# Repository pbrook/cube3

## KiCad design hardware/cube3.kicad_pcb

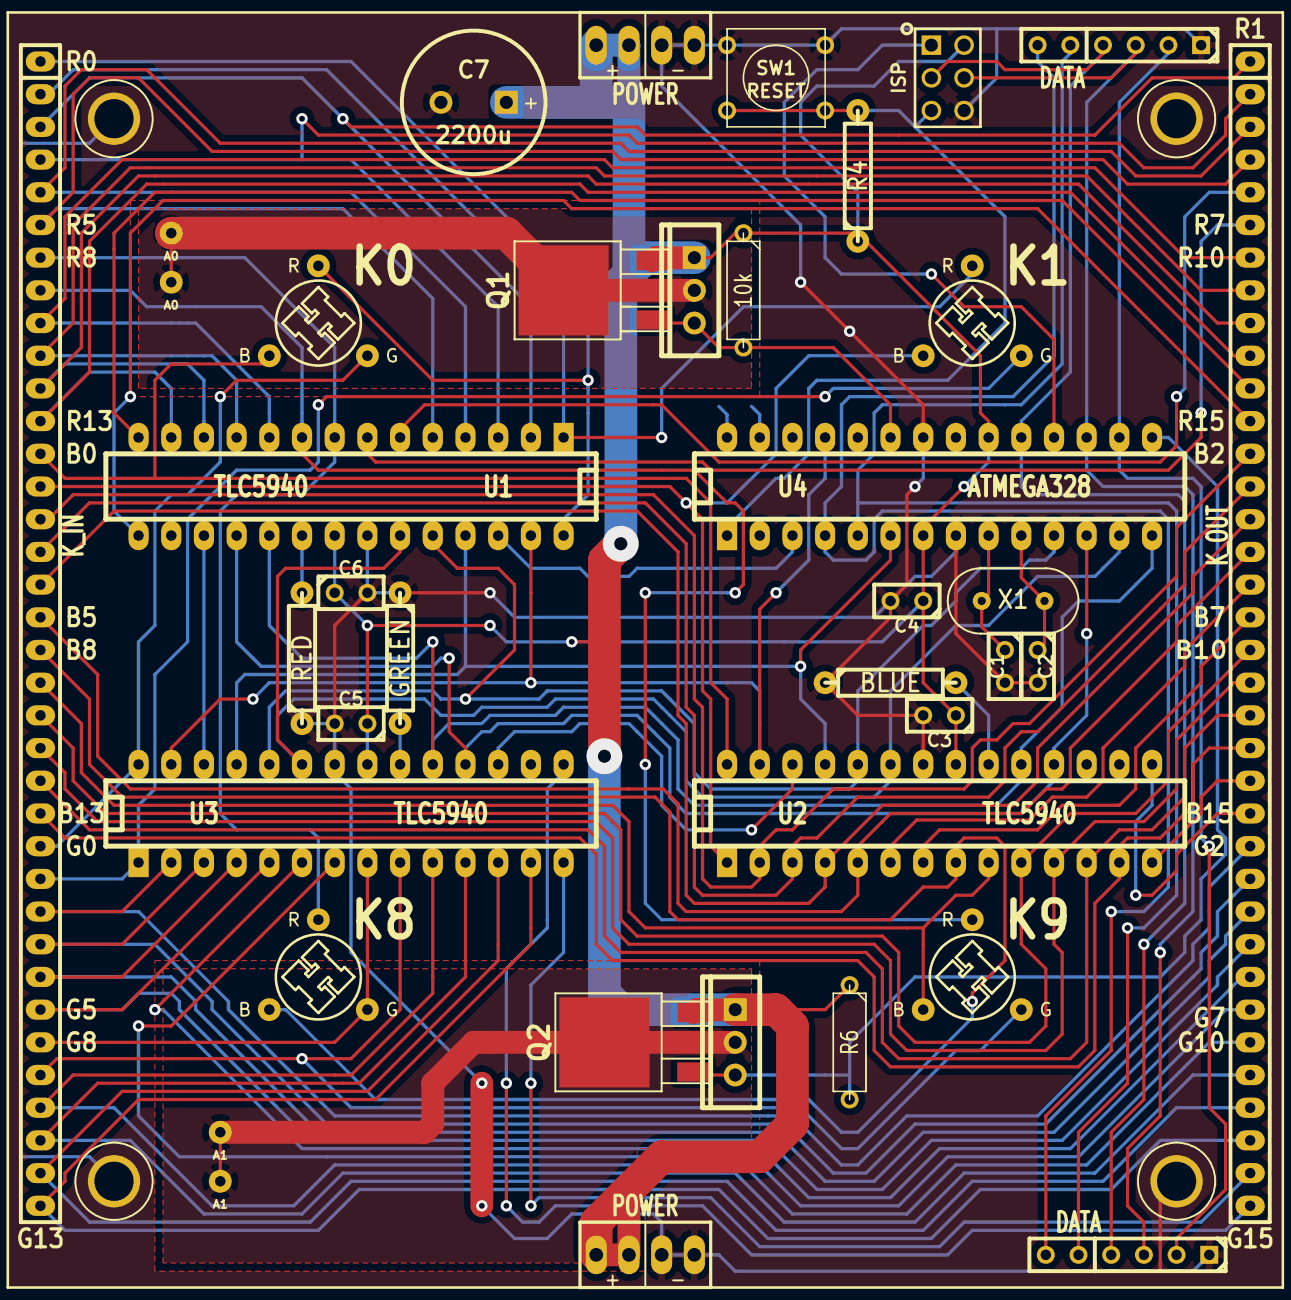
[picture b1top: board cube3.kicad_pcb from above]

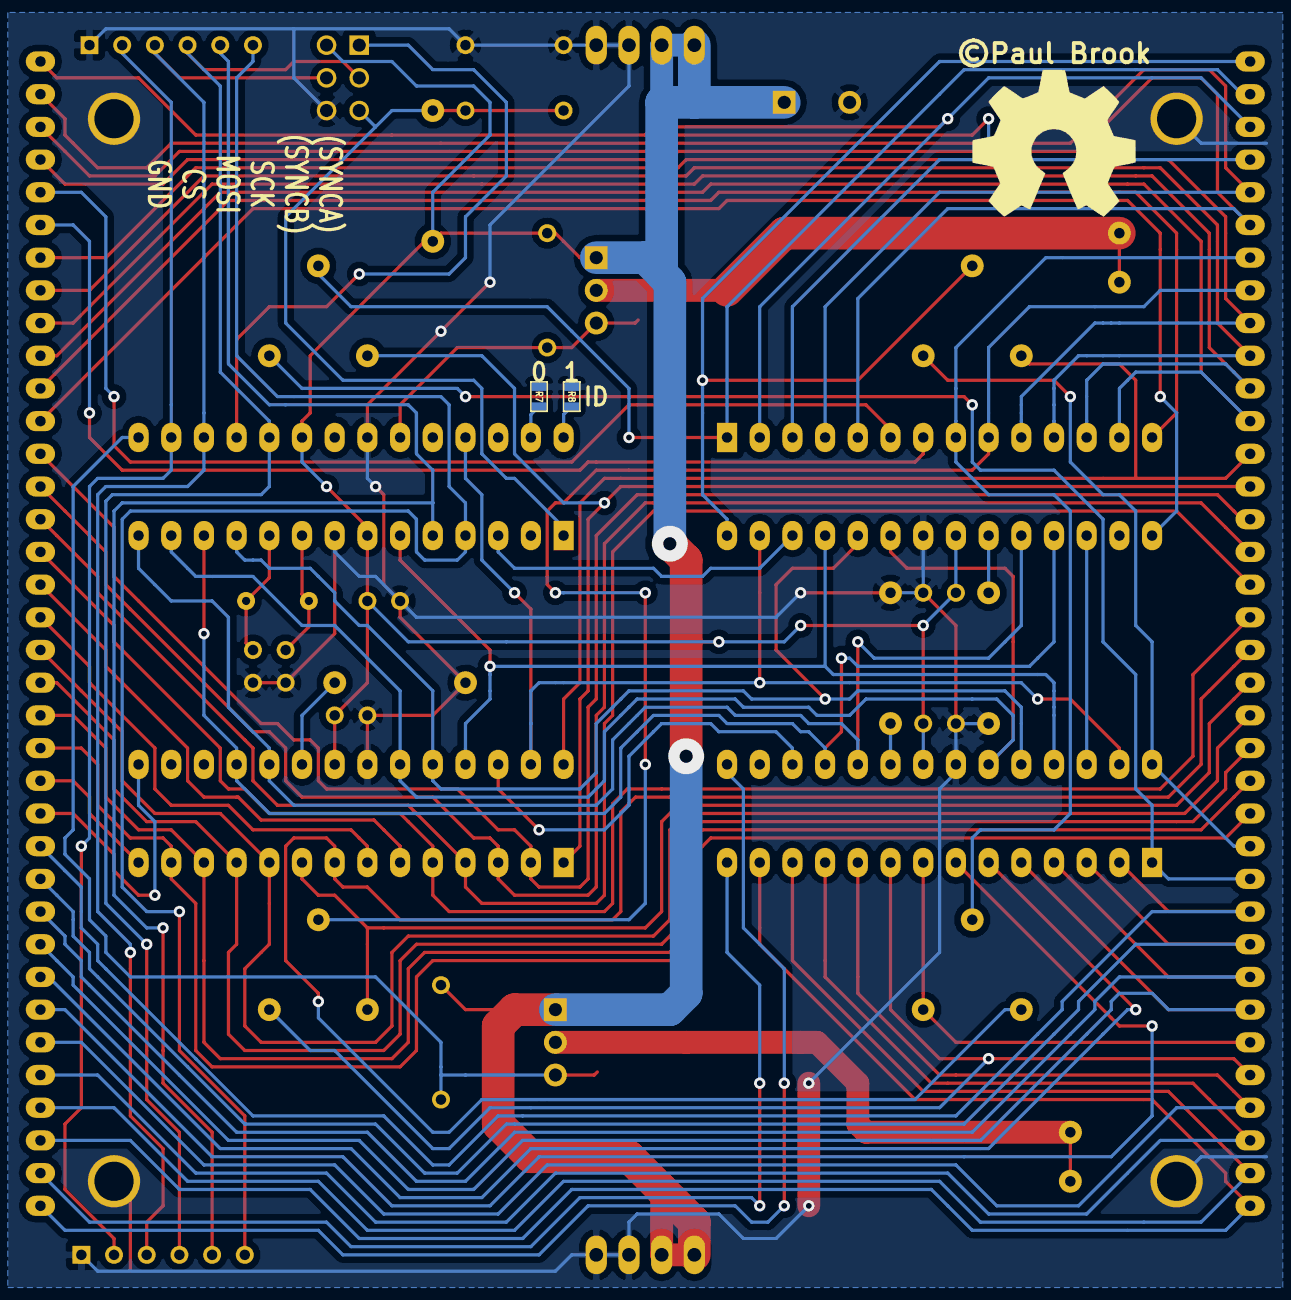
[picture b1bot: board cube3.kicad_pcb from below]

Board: 2 copper layers, 44 parts (2 on the bottom side), 77 nets.

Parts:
C1, C2: 22p; C1
C3, C4, C5, C6: 100n; C1
C7: 2200u; CP2V10
K0, K1, K8, K9: RGB_CATHODE; rgb_cathode
P1, P2: POWER; power2
P3, P4: DATA; SIL-6
P5: ISP; isp
P6, P7: A0; PIN1
P8, P15: A1; PIN1
P9: K_OUT; SIL-36
P10: K_IN; SIL-36
P11, P12, P13, P14: CONN_1; HOLE3
Q1, Q2: AP4435GH; to252
Q3, Q4: CONN_3; TO220_VERT
R1: RED; R4-LARGE_PADS
R2: BLUE; R4-LARGE_PADS
R3: GREEN; R4-LARGE_PADS
R4: 10k; R4-LARGE_PADS
R5, R6: 10k; R3-5
R7, R8: 0; SM0603
SW1: RESET; SW_PUSH_SMALL
U1, U2, U3: TLC5940; DIP-28__300_ELL
U4: ATMEGA328; DIP-28__300_ELL
X1: 16MHz; Crystal

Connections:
/5v: C3.1, C4.1, C5.1, C6.1, C7.1, P1.2, P2.2, P5.2, Q1.S, Q2.S, Q3.1, Q4.1, R4.1, R5.1, R6.1, U1.21, U2.21, U3.21, U4.7, U4.20
/A0: Q1.G, Q3.2, R5.2, U4.23
/A1: Q2.G, Q4.2, R6.2, U4.15
/BLANK: U1.23, U2.23, U3.23, U4.13
/BREF: R2.2, U2.20
/CS: P3.2, P4.2, U4.16
/DCPRG: U1.19, U2.19, U3.19, U4.14
/GND: C1.2, C2.2, C3.2, C4.2, C5.2, C6.2, C7.2, P1.1, P2.1, P3.1, P4.1, P5.6, P11.1, P12.1, P13.1, P14.1, R1.1, R2.1, R3.1, R7.1, R8.1, SW1.1, U1.22, U2.22, U3.22, U4.8, U4.22
/GREF: R3.2, U3.20
/GSCK: U1.18, U2.18, U3.18, U4.12
/H0: P6.1, P7.1, Q1.D, Q3.3
/H1: P8.1, P15.1, Q2.D, Q4.3
/ID0: R7.2, U4.27
/ID1: R8.2, U4.28
/MISO: P5.1, U4.18
/MOSI: P3.3, P4.3, P5.4, U4.17
/RESET: P5.5, R4.2, SW1.2, U4.1
/RREF: R1.2, U1.20
/SCK: P3.4, P4.4, P5.3, U4.19
/SCLK: U1.25, U2.25, U3.25, U4.6
/SIN: U1.26, U4.3
/SYNCA: P3.6, P4.6, U4.4
/SYNCB: P3.5, P4.5, U4.5
/VPRG: U1.27, U2.27, U3.27, U4.25
/XLAT: U1.24, U2.24, U3.24, U4.11
/b0: K0.B, P10.13, U2.28
/b1: K1.B, P10.14, U2.1
/b2: P9.13, P10.15, U2.2
/b3: P9.14, P10.16, U2.3
/b4: P9.15, P10.17, U2.4
/b5: P9.16, P10.18, U2.5
/b6: P9.17, U2.6
/b7: P9.18, U2.7
/b8: K8.B, P10.19, U2.8
/b9: K9.B, P10.20, U2.9
/b10: P9.19, P10.21, U2.10
/b11: P9.20, P10.22, U2.11
/b12: P9.21, P10.23, U2.12
/b13: P9.22, P10.24, U2.13
/b14: P9.23, U2.14
/b15: P9.24, U2.15
/g0: K0.G, P10.25, U3.28
/g1: K1.G, P10.26, U3.1
/g2: P9.25, P10.27, U3.2
/g3: P9.26, P10.28, U3.3
/g4: P9.27, P10.29, U3.4
/g5: P9.28, P10.30, U3.5
/g6: P9.29, U3.6
/g7: P9.30, U3.7
/g8: K8.G, P10.31, U3.8
/g9: K9.G, P10.32, U3.9
/g10: P9.31, P10.33, U3.10
/g11: P9.32, P10.34, U3.11
/g12: P9.33, P10.35, U3.12
/g13: P9.34, P10.36, U3.13
/g14: P9.35, U3.14
/g15: P9.36, U3.15
/r0: K0.R, P10.1, U1.28
/r1: K1.R, P10.2, U1.1
/r2: P9.1, P10.3, U1.2
/r3: P9.2, P10.4, U1.3
/r4: P9.3, P10.5, U1.4
/r5: P9.4, P10.6, U1.5
/r6: P9.5, U1.6
/r7: P9.6, U1.7
/r8: K8.R, P10.7, U1.8
/r9: K9.R, P10.8, U1.9
/r10: P9.7, P10.9, U1.10
/r11: P9.8, P10.10, U1.11
/r12: P9.9, P10.11, U1.12
/r13: P9.10, P10.12, U1.13
/r14: P9.11, U1.14
/r15: P9.12, U1.15
unnamed: C1.1, U4.9, X1.2
unnamed: C2.1, U4.10, X1.1
unnamed: U1.17, U3.26
unnamed: U2.26, U3.17

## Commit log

2014-05-12 Initial hardware design
2014-05-13 Final hardware tweaks.
2014-06-29 Initial firmware
2014-07-02 Firmware that actually works
2014-07-03 Reset serial link when unknown command encountered
2014-07-07 Add multi-board sync.
2014-07-08 Fix reset glitch
2014-07-08 Disable unused peripherals
2014-07-08 Process incoming data first
2014-07-08 Sleep mode
2014-07-08 Avoid sending data when idle.
2014-07-17 Fix race in sleep code.

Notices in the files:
hardware/cube3.kicad_pcb:
©Paul Brook
